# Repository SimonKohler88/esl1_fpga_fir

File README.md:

# esl1_fpga_fir
Configurable FIR for FPGA

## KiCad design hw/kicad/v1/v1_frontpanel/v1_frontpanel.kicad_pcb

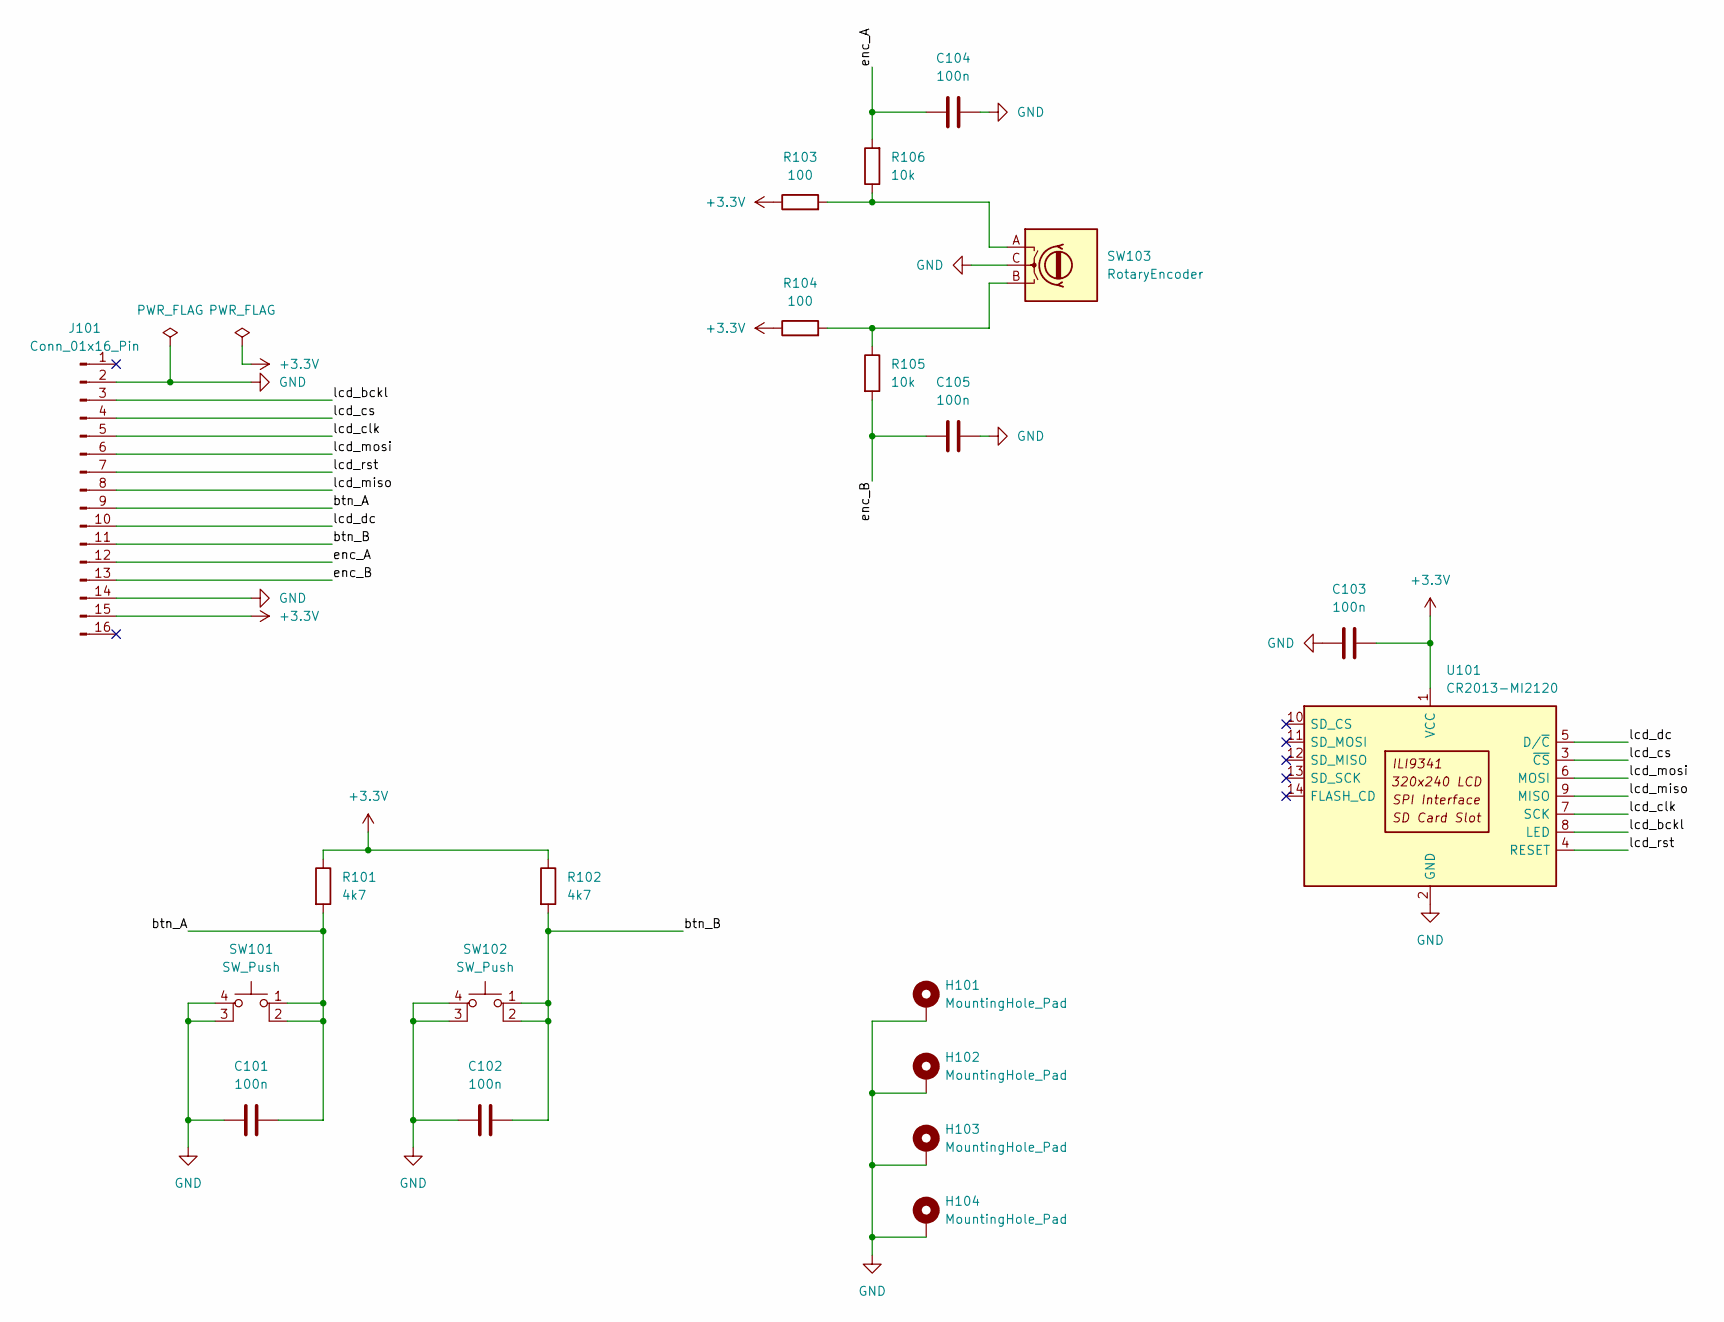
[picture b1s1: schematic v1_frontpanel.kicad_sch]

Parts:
C101, C102, C103, C104, C105: 100n; C_1206_3216Metric_Pad1.33x1.80mm_HandSolder
H101, H102, H103, H104: MountingHole_Pad; MountingHole_3.2mm_M3_DIN965_Pad
J101: Conn_01x16_Pin; PinHeader_2x08_P2.54mm_Vertical
R101, R102: 4k7; R_1206_3216Metric_Pad1.30x1.75mm_HandSolder
R103, R104: 100; R_1206_3216Metric_Pad1.30x1.75mm_HandSolder
R105, R106: 10k; R_1206_3216Metric_Pad1.30x1.75mm_HandSolder
SW101, SW102: SW_Push; Push_E-Switch_KS01Q01
SW103: RotaryEncoder; RotaryEncoder_Bourns_Vertical_PEC12R-3x17F-Nxxxx
U101: CR2013-MI2120

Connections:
+3.3V: C103.1, J101.15, R101.1, R102.1, R103.1, R104.1, U101.1 (VCC)
/btn_A: C101.2, J101.9, R101.2, SW101.1, SW101.2
/btn_B: C102.2, J101.11, R102.2, SW102.1, SW102.2
/enc_A: C104.2, J101.12, R106.2
/enc_B: C105.1, J101.13, R105.2
/lcd_bckl: J101.3, U101.8 (LED)
/lcd_clk: J101.5, U101.7 (SCK)
/lcd_cs: J101.4, U101.3 (~CS)
/lcd_dc: J101.10, U101.5 (D/~C)
/lcd_miso: J101.8, U101.9 (MISO)
/lcd_mosi: J101.6, U101.6 (MOSI)
/lcd_rst: J101.7, U101.4 (RESET)
GND: C101.1, C102.1, C103.2, C104.1, C105.2, H101.1, H102.1, H103.1, H104.1, J101.2, J101.14, SW101.3 (K), SW101.4 (A), SW102.3 (K), SW102.4 (A), SW103.C, U101.2 (GND)
unnamed: R103.2, R106.1, SW103.A
unnamed: R104.2, R105.1, SW103.B

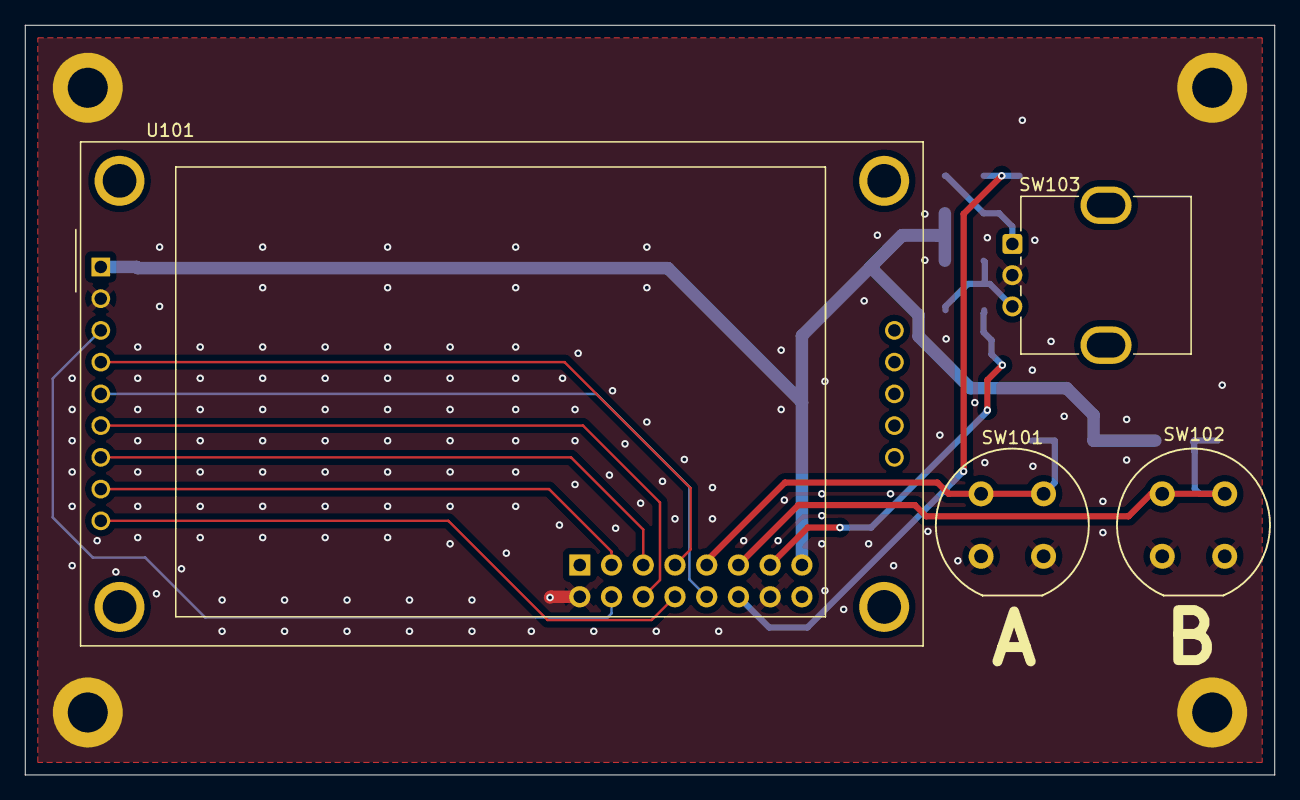
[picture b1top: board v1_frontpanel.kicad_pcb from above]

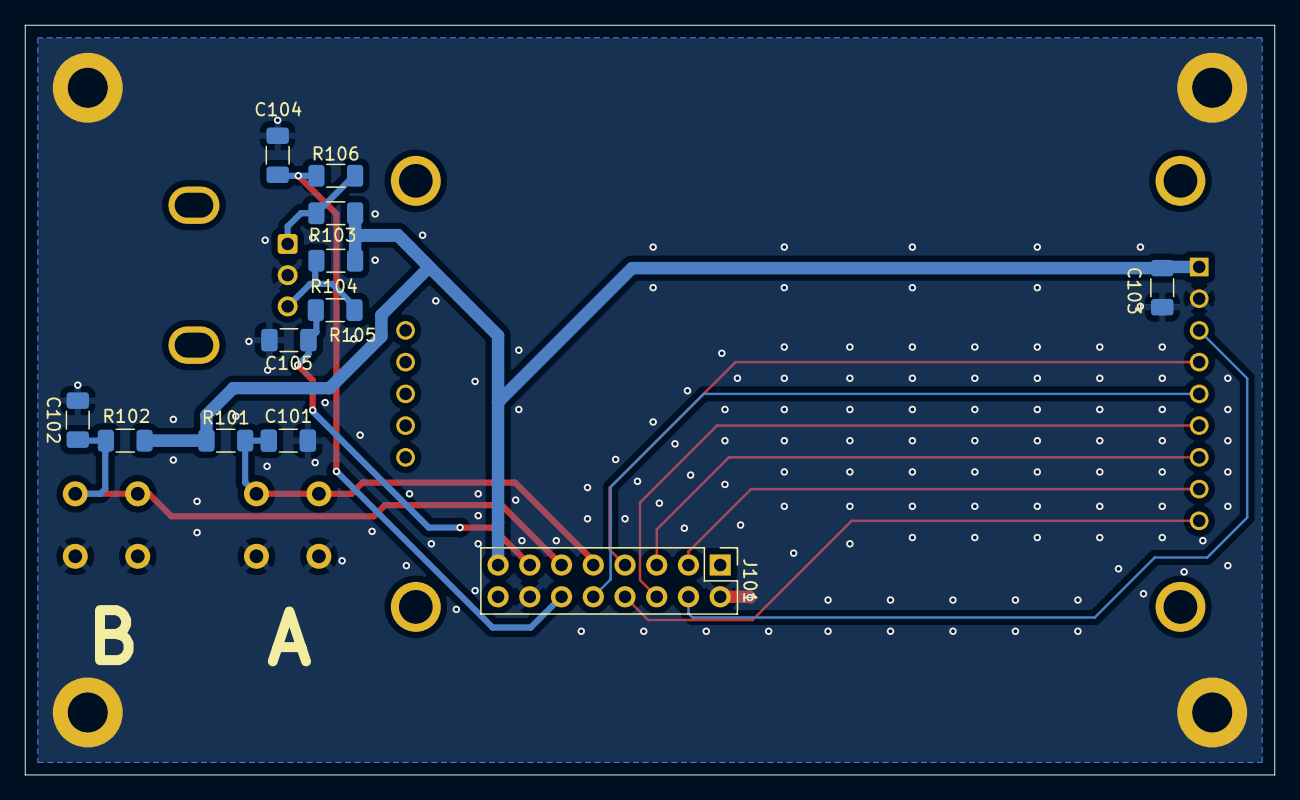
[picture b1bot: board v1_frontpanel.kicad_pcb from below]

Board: 2 copper layers, 100.0 x 60.0 mm, 20 parts (12 on the bottom side), 15 nets.

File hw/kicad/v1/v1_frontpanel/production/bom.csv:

Designator,Footprint,Quantity,Value,LCSC Part #
"C101, C102, C103, C104, C105",1206,5,100n,
J101,PinHeader_2x08_P2.54mm_Vertical,1,Conn_01x16_Pin,
"R101, R102",1206,2,4k7,
"R103, R104",1206,2,100,
"R105, R106",1206,2,10k,
"SW101, SW102",Push_E-Switch_KS01Q01,2,SW_Push,
SW103,RotaryEncoder_Bourns_Vertical_PEC12R-3x17F-Nxxxx,1,RotaryEncoder,
U101,CR2013-MI2120,1,CR2013-MI2120,

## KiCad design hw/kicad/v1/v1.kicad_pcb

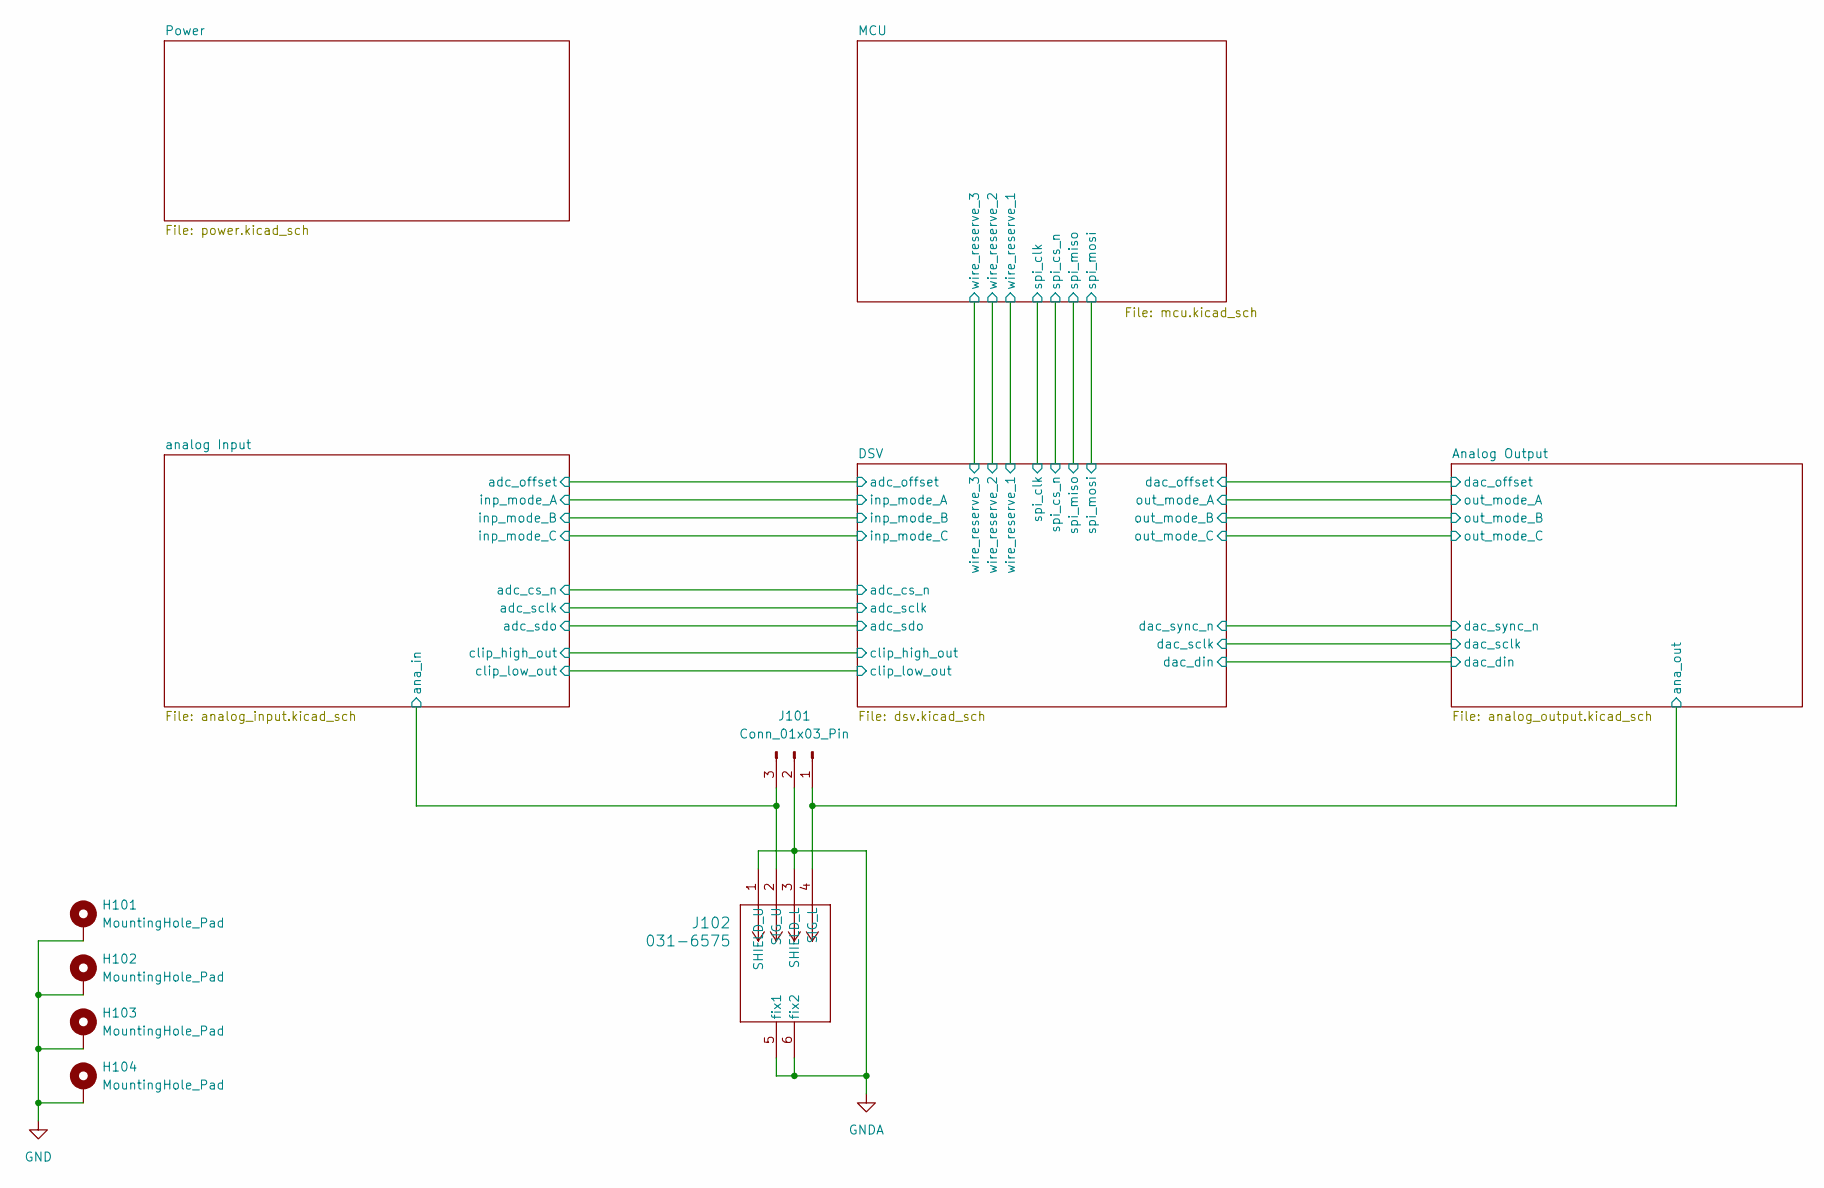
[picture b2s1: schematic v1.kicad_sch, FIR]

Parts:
H101, H102, H103, H104: MountingHole_Pad; MountingHole_3.2mm_M3_ISO7380_Pad_TopBottom
J101: Conn_01x03_Pin; PinHeader_1x03_P2.54mm_Horizontal
J102: 031-6575; CONN_6575_AMP

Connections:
/Analog Output/ana_out: J101.1, J102.4 (SIG_L); also elsewhere on the board
/analog Input/ana_in: J101.3, J102.2 (SIG_U); also elsewhere on the board
GND: H101.1, H102.1, H103.1, H104.1, J101.2, J102.1 (SHIELD_U), J102.3 (SHIELD_L), J102.5 (fix1), J102.6 (fix2); also elsewhere on the board

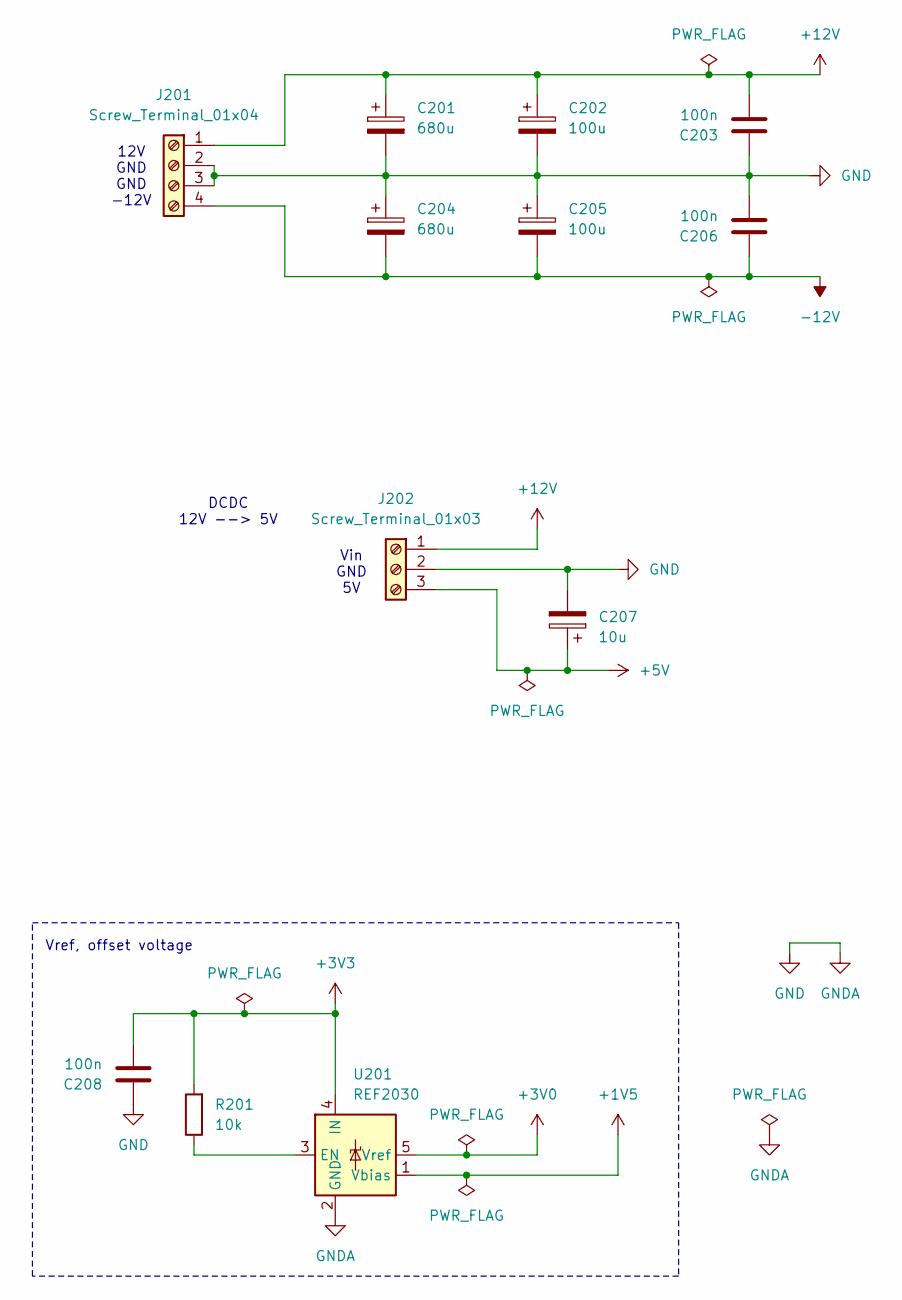
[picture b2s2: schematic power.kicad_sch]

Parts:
C201, C204: 680u; CP_Radial_D8.0mm_P5.00mm
C202, C205: 100u; CP_Radial_D8.0mm_P3.50mm
C203, C206, C208: 100n; C_1206_3216Metric_Pad1.33x1.80mm_HandSolder
C207: 10u; CP_Radial_D6.3mm_P2.50mm
J201: Screw_Terminal_01x04; TerminalBlock_MaiXu_MX126-5.0-04P_1x04_P5.00mm
J202: Screw_Terminal_01x03; TerminalBlock_MaiXu_MX126-5.0-03P_1x03_P5.00mm
R201: 10k; R_1206_3216Metric_Pad1.30x1.75mm_HandSolder
U201: REF2030; SOT-23-5

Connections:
+1V5: U201.1 (Vbias); also elsewhere on the board
+3V0: U201.5 (Vref); also elsewhere on the board
+3V3: C208.2, R201.2, U201.4 (IN); also elsewhere on the board
+5V: C207.1, J202.3; also elsewhere on the board
+12V: C201.1, C202.1, C203.2, J201.1, J202.1; also elsewhere on the board
-12V: C204.2, C205.2, C206.1, J201.4; also elsewhere on the board
GND: C201.2, C202.2, C203.1, C204.1, C205.1, C206.2, C207.2, C208.1, J201.2, J201.3, J202.2, U201.2 (GND); also elsewhere on the board
unnamed: R201.1, U201.3 (EN)

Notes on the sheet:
DCDC 12V --> 5V
Vin GND 5V
Vref, offset voltage
12V GND GND -12V

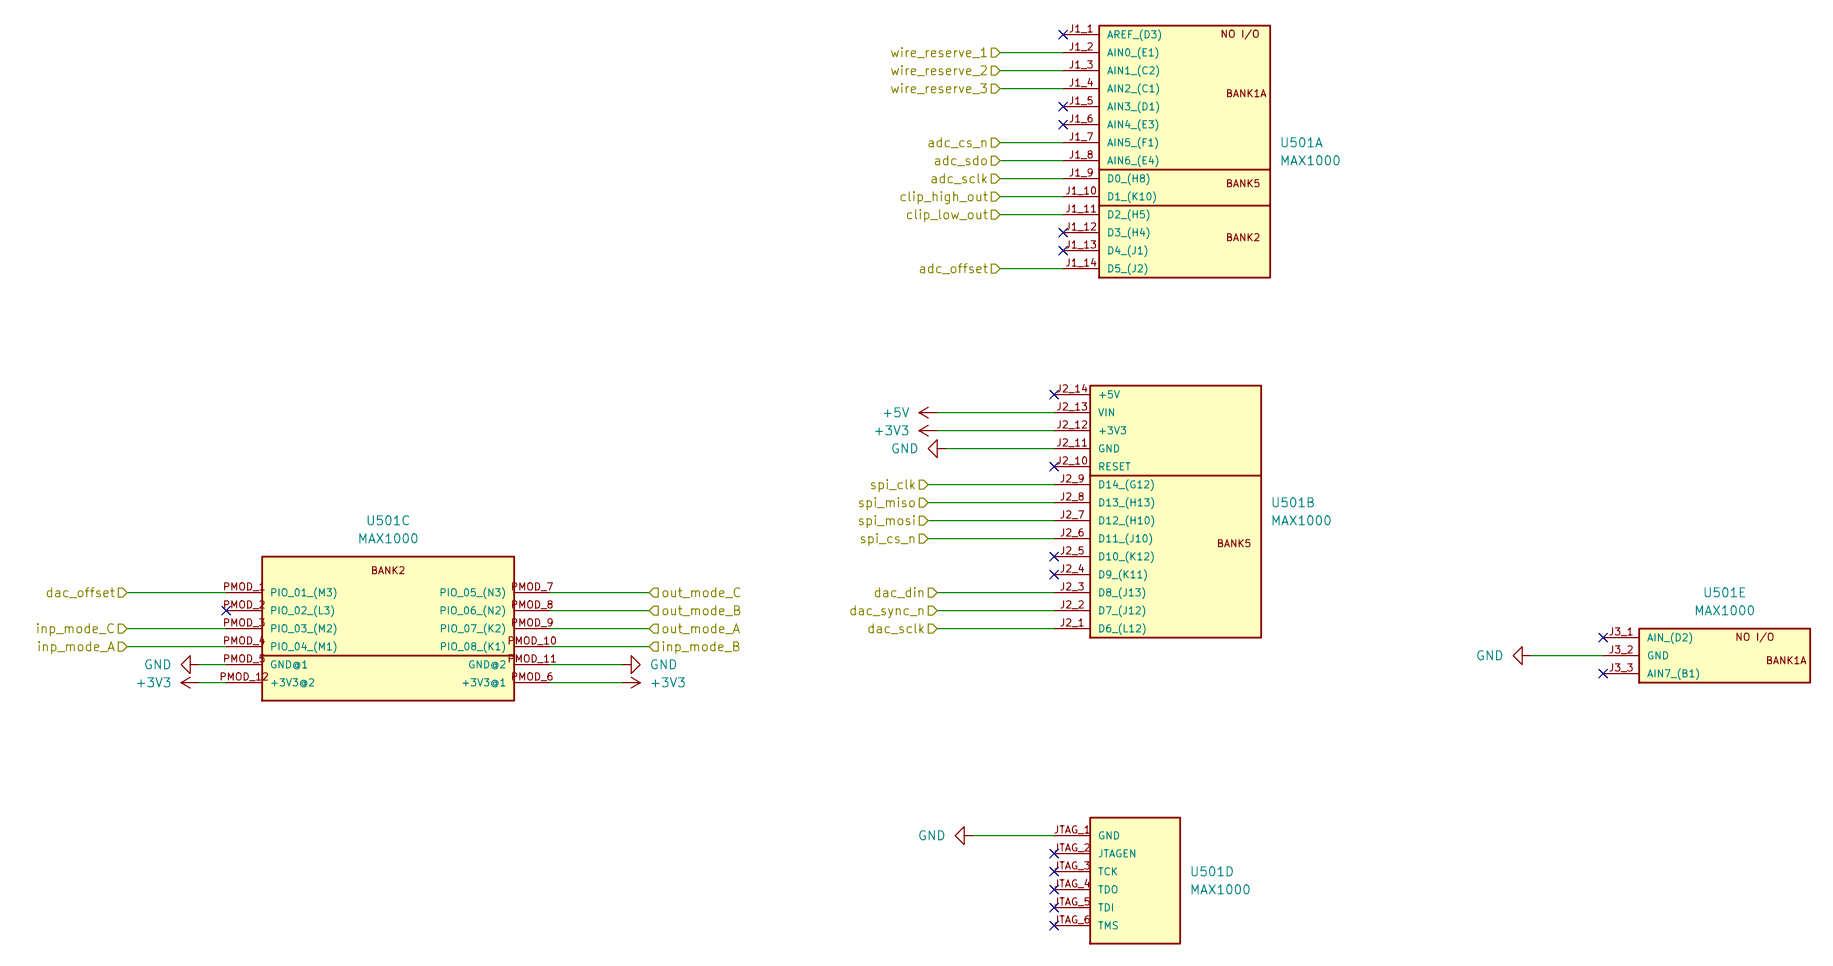
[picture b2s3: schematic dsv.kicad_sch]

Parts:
U501: MAX1000

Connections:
+3V3: U501.J2_12 (+3V3), U501.PMOD_6 (+3V3@1), U501.PMOD_12 (+3V3@2); also elsewhere on the board
+5V: U501.J2_13 (VIN); also elsewhere on the board
/Analog Output/dac_din: U501.J2_3 (D8_(J13)); also elsewhere on the board
/Analog Output/dac_offset: U501.PMOD_1 (PIO_01_(M3)); also elsewhere on the board
/Analog Output/dac_sclk: U501.J2_1 (D6_(L12)); also elsewhere on the board
/Analog Output/dac_sync_n: U501.J2_2 (D7_(J12)); also elsewhere on the board
/Analog Output/out_mode_A: U501.PMOD_9 (PIO_07_(K2)); also elsewhere on the board
/Analog Output/out_mode_B: U501.PMOD_8 (PIO_06_(N2)); also elsewhere on the board
/Analog Output/out_mode_C: U501.PMOD_7 (PIO_05_(N3)); also elsewhere on the board
/DSV/adc_cs_n: U501.J1_7 (AIN5_(F1)); also elsewhere on the board
/DSV/adc_offset: U501.J1_14 (D5_(J2)); also elsewhere on the board
/DSV/adc_sclk: U501.J1_9 (D0_(H8)); also elsewhere on the board
/DSV/adc_sdo: U501.J1_8 (AIN6_(E4)); also elsewhere on the board
/DSV/clip_high_out: U501.J1_10 (D1_(K10)); also elsewhere on the board
/DSV/clip_low_out: U501.J1_11 (D2_(H5)); also elsewhere on the board
/DSV/inp_mode_A: U501.PMOD_4 (PIO_04_(M1)); also elsewhere on the board
/DSV/inp_mode_B: U501.PMOD_10 (PIO_08_(K1)); also elsewhere on the board
/DSV/inp_mode_C: U501.PMOD_3 (PIO_03_(M2)); also elsewhere on the board
/DSV/spi_clk: U501.J2_9 (D14_(G12)); also elsewhere on the board
/DSV/spi_cs_n: U501.J2_6 (D11_(J10)); also elsewhere on the board
/DSV/spi_miso: U501.J2_8 (D13_(H13)); also elsewhere on the board
/DSV/spi_mosi: U501.J2_7 (D12_(H10)); also elsewhere on the board
/DSV/wire_reserve_1: U501.J1_2 (AIN0_(E1)); also elsewhere on the board
/DSV/wire_reserve_2: U501.J1_3 (AIN1_(C2)); also elsewhere on the board
/DSV/wire_reserve_3: U501.J1_4 (AIN2_(C1)); also elsewhere on the board
GND: U501.J2_11 (GND), U501.J3_2 (GND), U501.JTAG_1 (GND), U501.PMOD_5 (GND@1), U501.PMOD_11 (GND@2); also elsewhere on the board

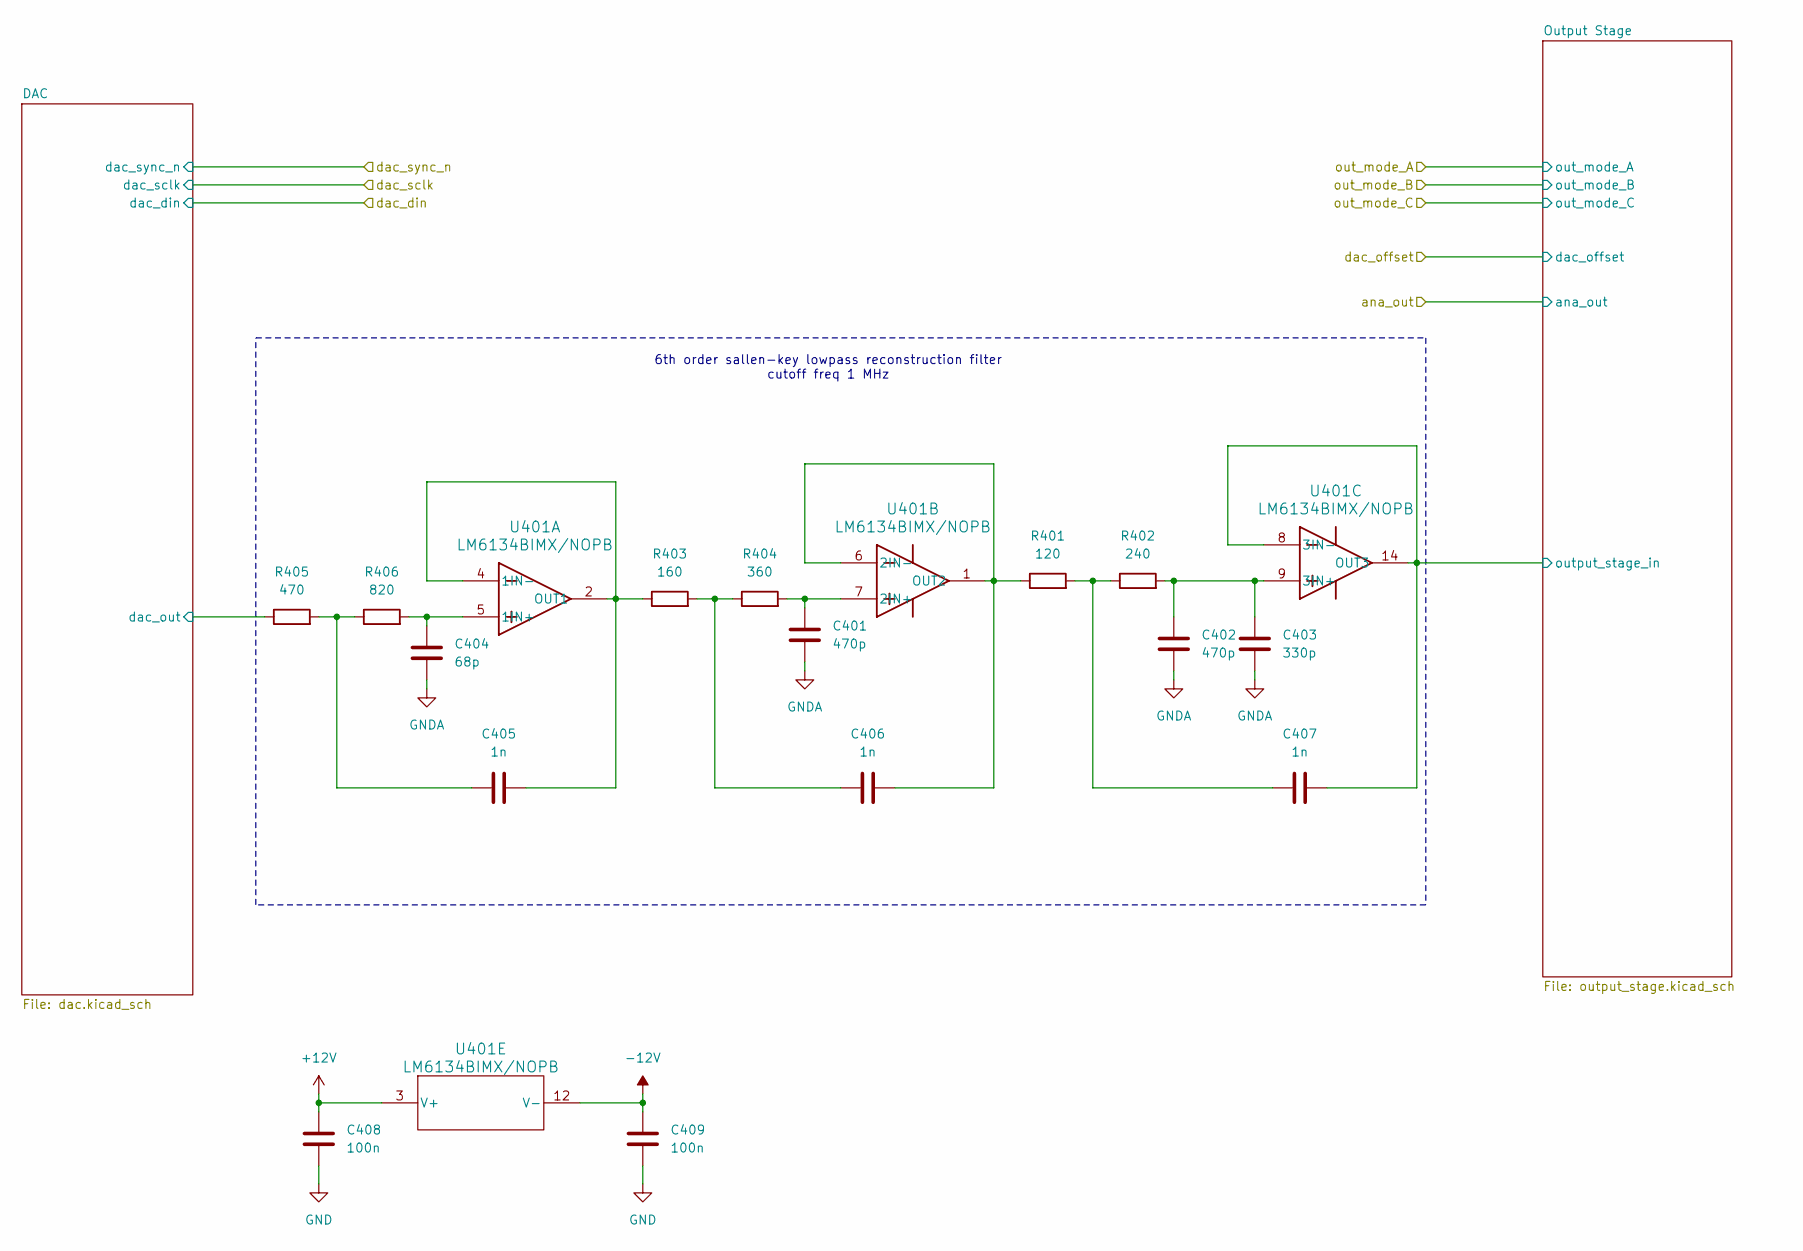
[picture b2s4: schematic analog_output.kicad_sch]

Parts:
C401, C402: 470p; C_0603_1608Metric_Pad1.08x0.95mm_HandSolder
C403: 330p; C_0603_1608Metric_Pad1.08x0.95mm_HandSolder
C404: 68p; C_0603_1608Metric_Pad1.08x0.95mm_HandSolder
C405, C406, C407: 1n; C_1206_3216Metric_Pad1.33x1.80mm_HandSolder
C408, C409: 100n; C_1206_3216Metric_Pad1.33x1.80mm_HandSolder
R401: 120; R_1206_3216Metric_Pad1.30x1.75mm_HandSolder
R402: 240; R_1206_3216Metric_Pad1.30x1.75mm_HandSolder
R403: 160; R_1206_3216Metric_Pad1.30x1.75mm_HandSolder
R404: 360; R_1206_3216Metric_Pad1.30x1.75mm_HandSolder
R405: 470; R_1206_3216Metric_Pad1.30x1.75mm_HandSolder
R406: 820; R_1206_3216Metric_Pad1.30x1.75mm_HandSolder
U401: LM6134BIMX/NOPB; SOIC-14_3.9x8.7mm_P1.27mm

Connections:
+12V: C408.1, U401.3 (V+); also elsewhere on the board
-12V: C409.1, U401.12 (V-); also elsewhere on the board
/Analog Output/DAC/dac_out: R405.1; also elsewhere on the board
/Analog Output/Output Stage/output_stage_in: C407.2, U401.8 (3IN-), U401.14 (OUT3); also elsewhere on the board
GND: C401.2, C402.2, C403.2, C404.2, C408.2, C409.2; also elsewhere on the board
unnamed: C405.1, R405.2, R406.1
unnamed: C406.1, R403.2, R404.1
unnamed: C407.1, R401.2, R402.1
unnamed: C404.1, R406.2, U401.5 (1IN+)
unnamed: C405.2, R403.1, U401.2 (OUT1), U401.4 (1IN-)
unnamed: C401.1, R404.2, U401.7 (2IN+)
unnamed: C406.2, R401.1, U401.1 (OUT2), U401.6 (2IN-)
unnamed: C402.1, C403.1, R402.2, U401.9 (3IN+)

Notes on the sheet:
6th order sallen-key lowpass reconstruction filter cutoff freq 1 MHz

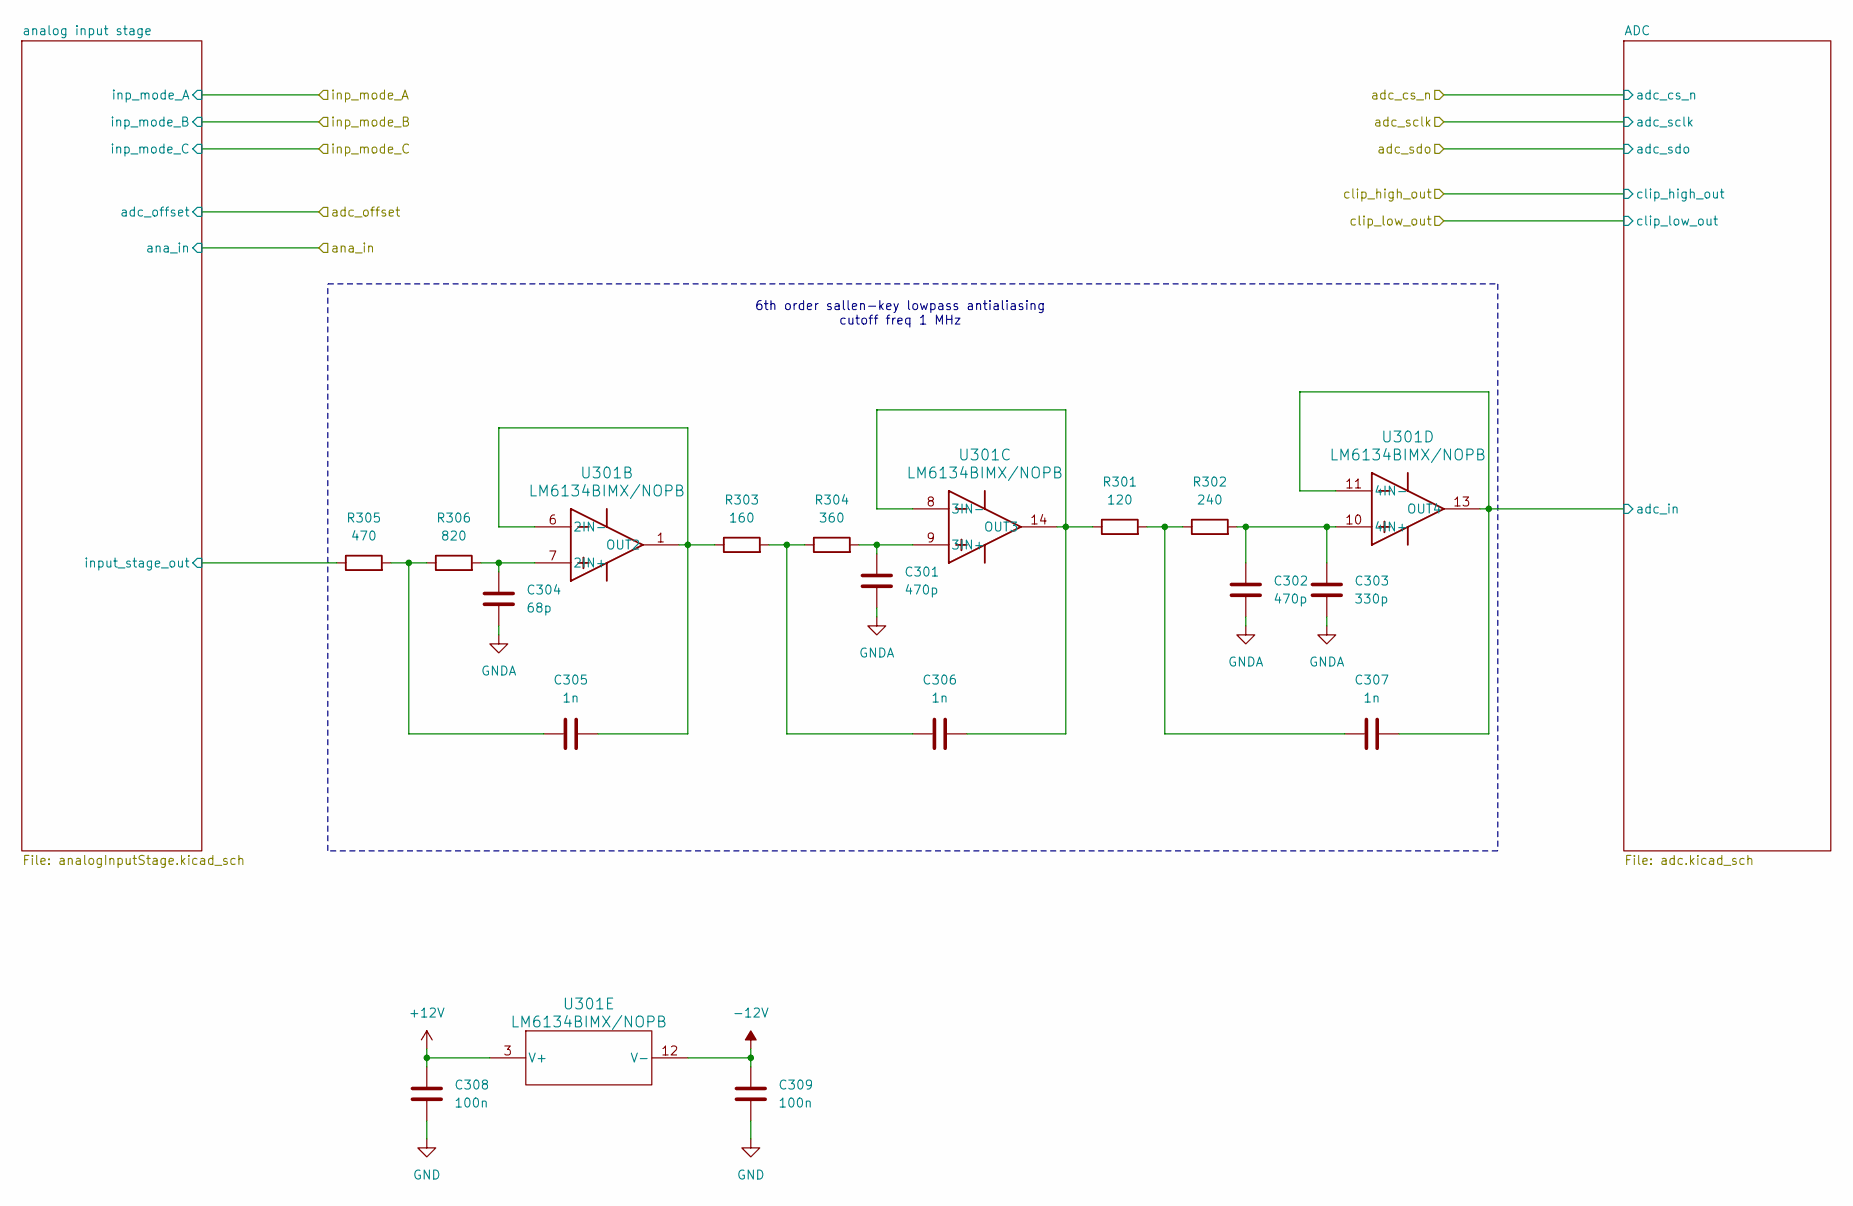
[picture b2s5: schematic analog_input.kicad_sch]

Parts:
C301, C302: 470p; C_0603_1608Metric_Pad1.08x0.95mm_HandSolder
C303: 330p; C_0603_1608Metric_Pad1.08x0.95mm_HandSolder
C304: 68p; C_0603_1608Metric_Pad1.08x0.95mm_HandSolder
C305, C306, C307: 1n; C_1206_3216Metric_Pad1.33x1.80mm_HandSolder
C308, C309: 100n; C_1206_3216Metric_Pad1.33x1.80mm_HandSolder
R301: 120; R_1206_3216Metric_Pad1.30x1.75mm_HandSolder
R302: 240; R_1206_3216Metric_Pad1.30x1.75mm_HandSolder
R303: 160; R_1206_3216Metric_Pad1.30x1.75mm_HandSolder
R304: 360; R_1206_3216Metric_Pad1.30x1.75mm_HandSolder
R305: 470; R_1206_3216Metric_Pad1.30x1.75mm_HandSolder
R306: 820; R_1206_3216Metric_Pad1.30x1.75mm_HandSolder
U301: LM6134BIMX/NOPB; SOIC-14_3.9x8.7mm_P1.27mm

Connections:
+12V: C308.1, U301.3 (V+); also elsewhere on the board
-12V: C309.1, U301.12 (V-); also elsewhere on the board
/analog Input/ADC/adc_in: C307.2, U301.11 (4IN-), U301.13 (OUT4); also elsewhere on the board
/analog Input/analog input stage/input_stage_out: R305.1; also elsewhere on the board
GND: C301.2, C302.2, C303.2, C304.2, C308.2, C309.2; also elsewhere on the board
unnamed: C305.1, R305.2, R306.1
unnamed: C306.1, R303.2, R304.1
unnamed: C307.1, R301.2, R302.1
unnamed: C304.1, R306.2, U301.7 (2IN+)
unnamed: C305.2, R303.1, U301.1 (OUT2), U301.6 (2IN-)
unnamed: C301.1, R304.2, U301.9 (3IN+)
unnamed: C306.2, R301.1, U301.8 (3IN-), U301.14 (OUT3)
unnamed: C302.1, C303.1, R302.2, U301.10 (4IN+)

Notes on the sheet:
6th order sallen-key lowpass antialiasing cutoff freq 1 MHz
